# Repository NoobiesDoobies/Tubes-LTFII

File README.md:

# Tubes-LTFII

Problem: 
1. End Effector not rigid enough
2. Motor cannot overcome friction from the pen
3. IK cannot respond to rapid changes in coordinate

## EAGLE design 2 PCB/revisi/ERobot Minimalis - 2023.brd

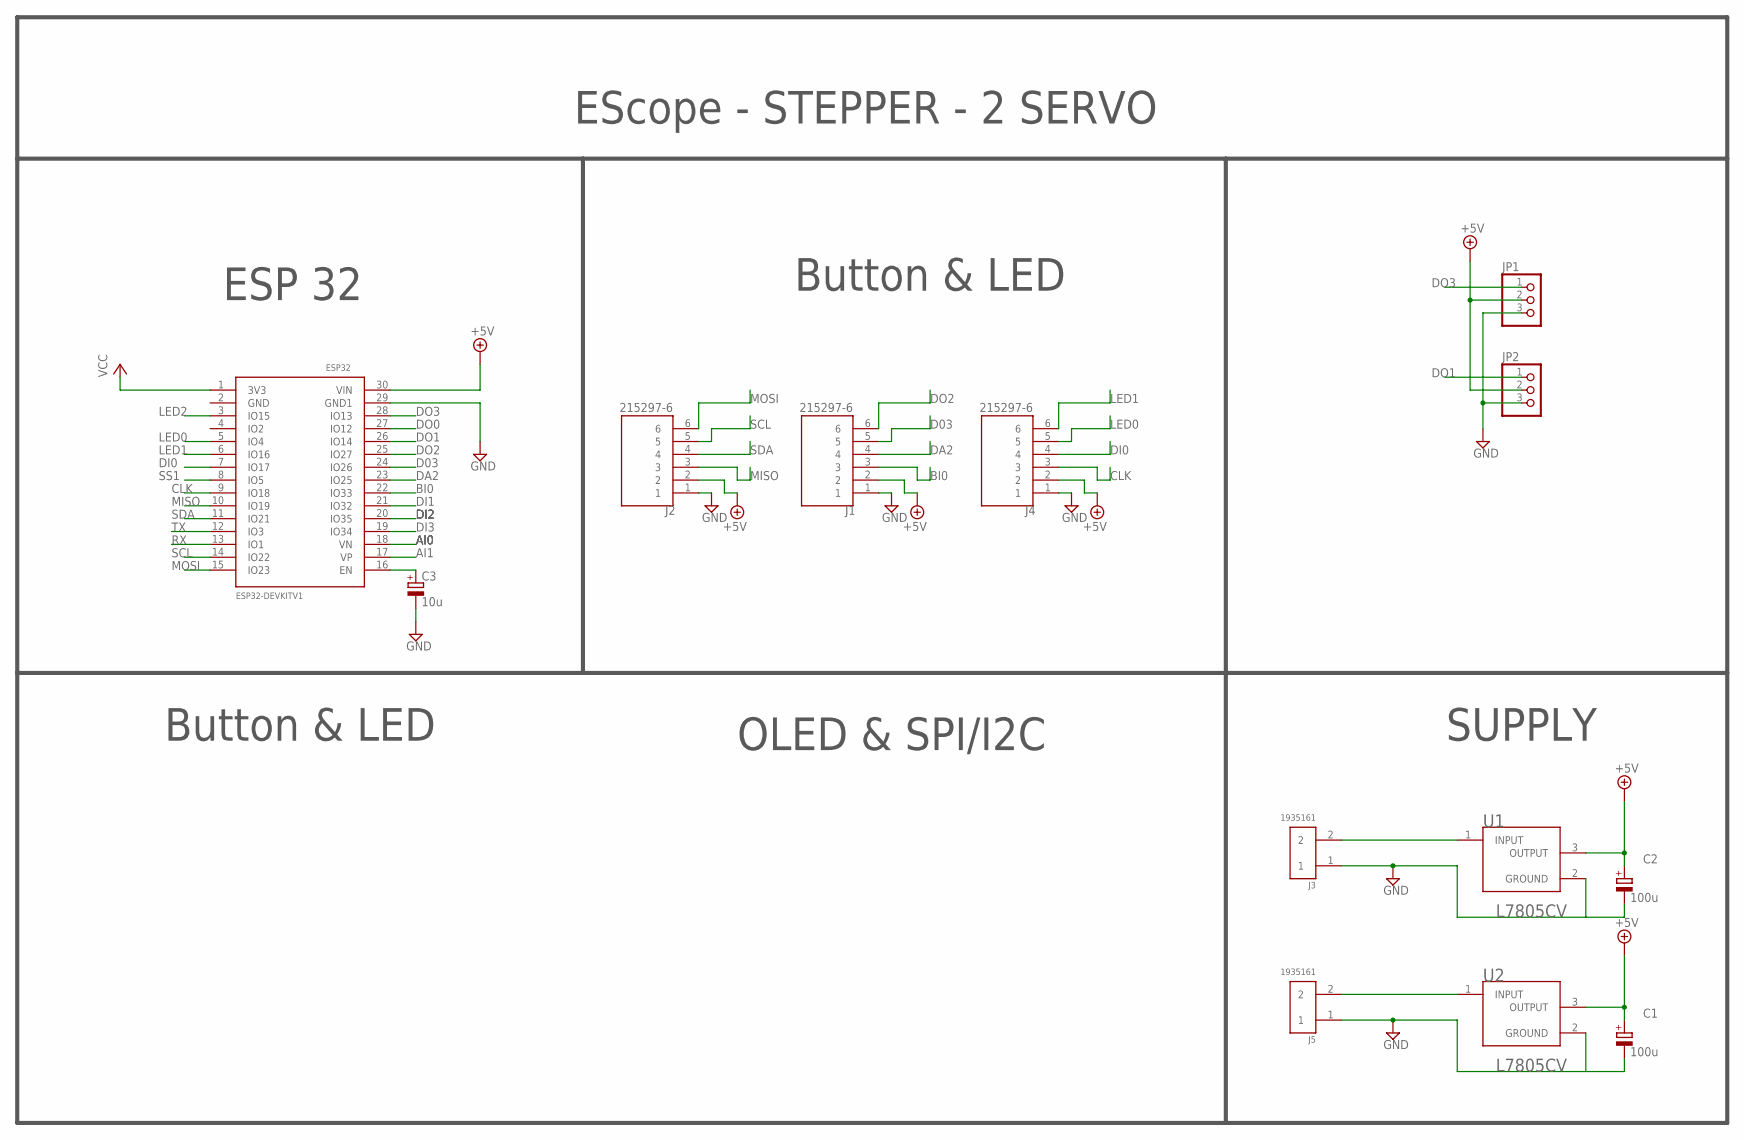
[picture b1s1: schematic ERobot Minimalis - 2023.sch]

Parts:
C1, C2: 100u; E3,5-8
C3: 10u; E2,5-5
ESP32: DEVKIT-V1; ESP32-DEVKITV1
J1, J2, J4: 215297-6; TE_215297-6
J3, J5: 1935161; PHOENIX_1935161
JP1, JP2: PINHD-1X3; 1X03
U1, U2: STMICROELECTRONICS_L7805CVSTMICROELECTRONICS_L780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; STMICROELECTRONICS_L7805CV_0

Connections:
+5V: C1.+, C2.+, ESP32.30 (VIN), J1.2, J2.2, J4.2, JP1.2, JP2.2, U1.3 (OUTPUT), U2.3 (OUTPUT)
AI0: ESP32.18 (VN)
AI1: ESP32.17 (VP)
BI0: ESP32.22 (IO33), J1.3
CLK: ESP32.9 (IO18), J4.3
D03: ESP32.24 (IO26), J1.5
DA2: ESP32.23 (IO25), J1.4
DI0: ESP32.7 (IO17), J4.4
DI1: ESP32.21 (IO32)
DI2: ESP32.20 (IO35)
DI3: ESP32.19 (IO34)
DO0: ESP32.27 (IO12)
DO1: ESP32.26 (IO14), JP2.1
DO2: ESP32.25 (IO27), J1.6
DO3: ESP32.28 (IO13), JP1.1
GND: C1.-, C2.-, C3.-, ESP32.29 (GND1), J1.1, J2.1, J3.1, J4.1, J5.1, JP1.3, JP2.3, U1.2 (GROUND), U2.2 (GROUND)
LED0: ESP32.5 (IO4), J4.5
LED1: ESP32.6 (IO16), J4.6
LED2: ESP32.3 (IO15)
MISO: ESP32.10 (IO19), J2.3
MOSI: ESP32.15 (IO23), J2.6
unnamed: J5.2, U2.1 (INPUT)
unnamed: J3.2, U1.1 (INPUT)
unnamed: C3.+, ESP32.16 (EN)
RX: ESP32.13 (IO1)
SCL: ESP32.14 (IO22), J2.5
SDA: ESP32.11 (IO21), J2.4
SS1: ESP32.8 (IO5)
TX: ESP32.12 (IO3)
VCC: ESP32.1 (3V3)

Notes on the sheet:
ESP 32
SUPPLY
Button & LED
EScope - STEPPER - 2 SERVO
OLED & SPI/I2C

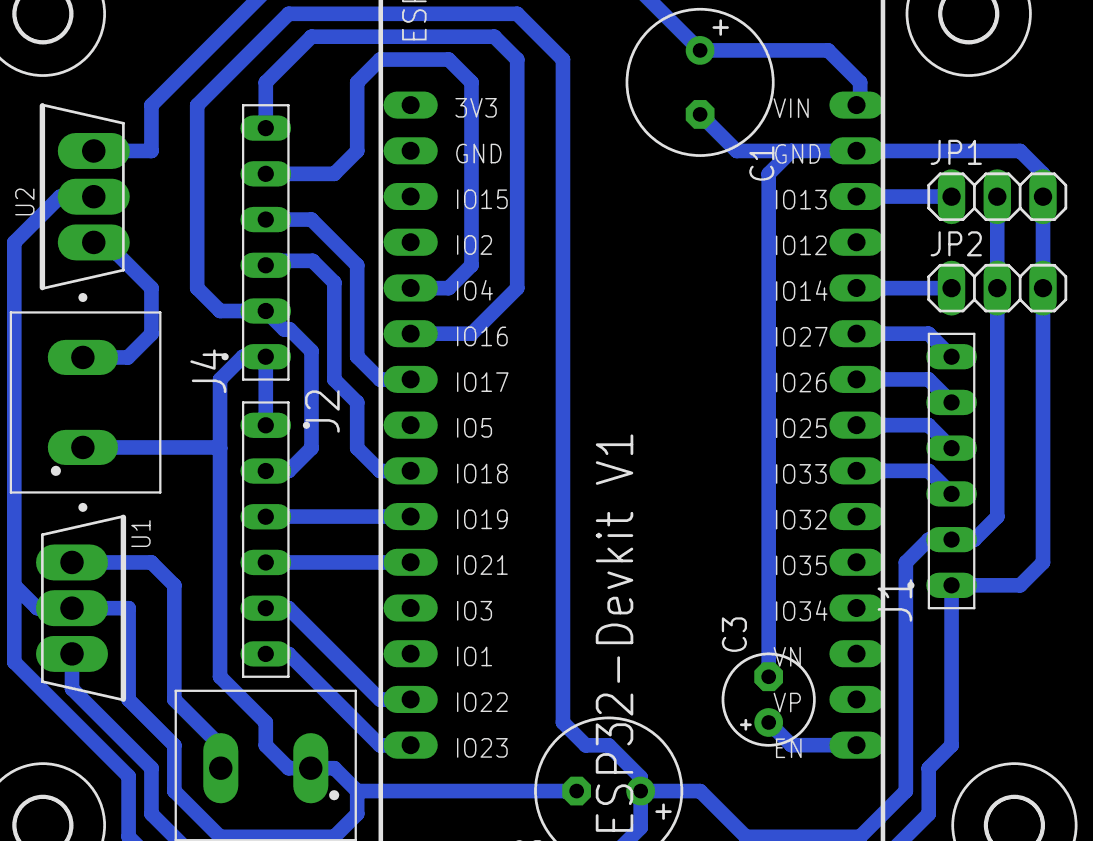
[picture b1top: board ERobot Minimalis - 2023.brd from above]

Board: 2 copper layers, 17 parts (0 on the bottom side), 19 nets.

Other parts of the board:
U$2, U$3, U$4, U$5: 3,0

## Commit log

2023-03-27 initial commit, joystick done, can now spam button
2023-03-30 add kalibrasi and mode switching
2023-03-30 Create CAD
2023-03-30 masih nyoba
    tutorial hiks
2023-03-30 Referensi CAD
    inii referensi yg dikasi asprakk, mungkin baiknya ga diotak atik gitu, nti file2 yg dibutuhin dicopy ke folder "Eksekusi" ajah :D
2023-03-30 Referensi format sldrpt
    ternyata didalem foldernya ada zip file2 yg bentukannya sldrpt
2023-03-30 Copas beberapa part
    ini kek baru copas2 seklias kira2 part yg dibutuhin apa + nyoba bikin arm, sama mo nanya ini basenya jadi pake gear atau ngikutin referensi aja (lgsg dibaut ke baling2 servo)?
2023-04-01 Hole left hand sesuai kipas
    cuma bolongin tangannya sesuai bentuk kipas (referensi me arm uro)
2023-04-01 add wifi module esp
2023-04-01 done joystick API
2023-04-02 Base
    ini ukurannya masi ngasal
2023-04-02 Arm 1
    nyoba buat arm 1
2023-04-02 Arm 2
    nyoba arm2an haduch, btw ini fastener2nya sementara bikin kek tabung aja kli ya biar gampang? trus pegangan pena sm assembly beloman hiks
2023-04-02 add ktor and okhttp
    still cannot post
2023-04-03 asembli
    coba github
2023-04-03 done wifi communication in controller app folder
2023-04-05 added mode switching
2023-04-05 add mode switching
2023-04-05 Upper base rev 1
    ini upper base yang fixnya
2023-04-05 Arm dan Gear
    agak bingung mounting :)
2023-04-06 add slider layout
2023-04-06 Create catatan
2023-04-06 Rename Skematik/catatan to PCB/catatan
2023-04-06 Assembly dan mounting
    masi nyoba
2023-04-06 gear stepper
2023-04-06 added joystick
2023-04-06 add controller update UI
2023-04-06 fix switch screen bug
2023-04-06 Revisi dan Fiksasi
    yak jadi setelah revisi sana sini yagesya. + file yg namanya [FIX] kemungkinan gaada perubahan lagi
2023-04-06 rename folder
2023-04-06 rename file ino
2023-04-06 Revisi diameter shaft
    diameter yang tadinya 12.5 mm jadi 8.25mm
2023-04-06 gear sebelah motor
2023-04-06 motor sebelah gear diameter 8.25mm
2023-04-06 esp parsing query params from android
    able to parse based on mode: Arrows, JoyStick, Slider
2023-04-06 change variable name
2023-04-07 Revisi panjang arm
    keknya perlu disesuaiin lagi ntar hem
2023-04-08 Fiksasi Base
    harusnya udh siap print
2023-04-08 coba gear
2023-04-08 arm 1 lebih tinggi
2023-04-08 asembli jam 2
2023-04-08 asembli 14.08
2023-04-08 Gear V3
2023-04-08 Penopang Stepper
    supaya pulley setara
2023-04-08 integrate app and actuator
2023-04-08 remove unnecessary UI in slider layout
2023-04-08 Fiksasi Penopang
    hehe
2023-04-08 gear upper base
2023-04-08 asembly gear baru
2023-04-08 add synchronise, but slow
2023-04-08 Assembly hampir final
    capek ges
2023-04-09 Revisian Zoom
    ini itu persiapan printing
2023-04-09 Gear V4
2023-04-09 Persiapan print 1
    semua kecuali arm 2
2023-04-10 gear V4 tebal 1.5 cm
2023-04-10 Revisi Mounting
    hehe
2023-04-10 gear fix
2023-04-10 Revisi lubang2 baut 3d print
2023-04-10 Folder print WS
2023-04-10 zip folder buat ws
2023-04-10 Drawing Laser cut
    lupa push maap
2023-04-10 revisi mekanik
2023-04-11 mounting lengan
2023-04-11 revisi lubang vertikal spidol
2023-04-11 Submit 3D print ke WS Revisi 1
2023-04-11 tebelin base
2023-04-11 revisi tempat clamp spidol dan slot vertikal
2023-04-11 revisi 2
2023-04-12 revisi pin vertikal
2023-04-12 revisi pin spidol vertikal
2023-04-12 revisi pin spidol vertikal dan silindernya lagi
2023-04-12 ganti ukuran lubang pin spidol ke 2.5mm
2023-04-12 ukuran lubang pin spidol ganti ke 2.5 mm
2023-04-12 revisi base (motor masuk)
2023-04-12 Submit revisi 2 final
2023-04-12 naikin size dynamic json
2023-04-12 fix some bugs
2023-04-12 revisi bagian spidol
2023-04-12 Revisi 3
    monggo lanjutin gab
2023-04-12 assembly semuanya
2023-04-13 revisi Gab 2.5mm
2023-04-13 sejajarin lubang base
2023-04-13 Revisi arm 1, arm 2, tempat servo spidol
    revisi diameter ges
2023-04-17 revisi di URO
2023-04-17 tambahan di URO
2023-04-18 revisi gir kecil pulley
2023-04-18 Add penahan
2023-04-18 fix view null bug
2023-04-18 add test actuator code
2023-04-18 integrating
2023-04-19 move x,y,z var to global
2023-04-19 fix sendDataToESP bug
    sendDataToESP keep getting called within coroutine even though it already switches to another activity
2023-04-19 fix slider calibrating bug
2023-04-20 set offset
2023-04-22 fix calibrate (again)
2023-04-22 done testing, still shaky
2023-04-23 benerin assem dan add new pen holder
2023-04-23 perfecting dimension for end effector
2023-04-23 add pen holder to assembly
2023-04-23 add to print folder
2023-04-24 change file name and delete unnecessary files
2023-04-24 slice pen holder and others
2023-04-25 revisi PCB
2023-04-25 update arm1 dan arm2 CAD
2023-04-25 revisi arm2 dikit
2023-04-25 revisi arm1 sedikit, geser lubang shaft
2023-04-25 geser lagi
2023-04-25 revisi 3 corel
2023-04-25 revisi 4 corel
2023-04-26 tambah 1 baterai PCB
2023-04-26 jadiin zip buat print dan cut
2023-04-26 geser lubang arm2 lagi
2023-04-26 3d Board PCB
2023-04-26 ngapusin corel yg ga guna
2023-04-26 laser cut rev 5 6
2023-04-26 hapusin yg gaperlu
2023-04-26 zip laser cut
2023-04-27 tambah STEP
2023-04-28 update BASE
2023-04-28 Laser Cut BASE
2023-04-28 BASE Laser Cut
2023-05-02 redesign servo housing to make it longer
2023-05-04 export APK
2023-05-15 add gear kecil edge tegak dan radius benar
2023-05-22 final push
2023-05-28 terakhir kali ganti SW
